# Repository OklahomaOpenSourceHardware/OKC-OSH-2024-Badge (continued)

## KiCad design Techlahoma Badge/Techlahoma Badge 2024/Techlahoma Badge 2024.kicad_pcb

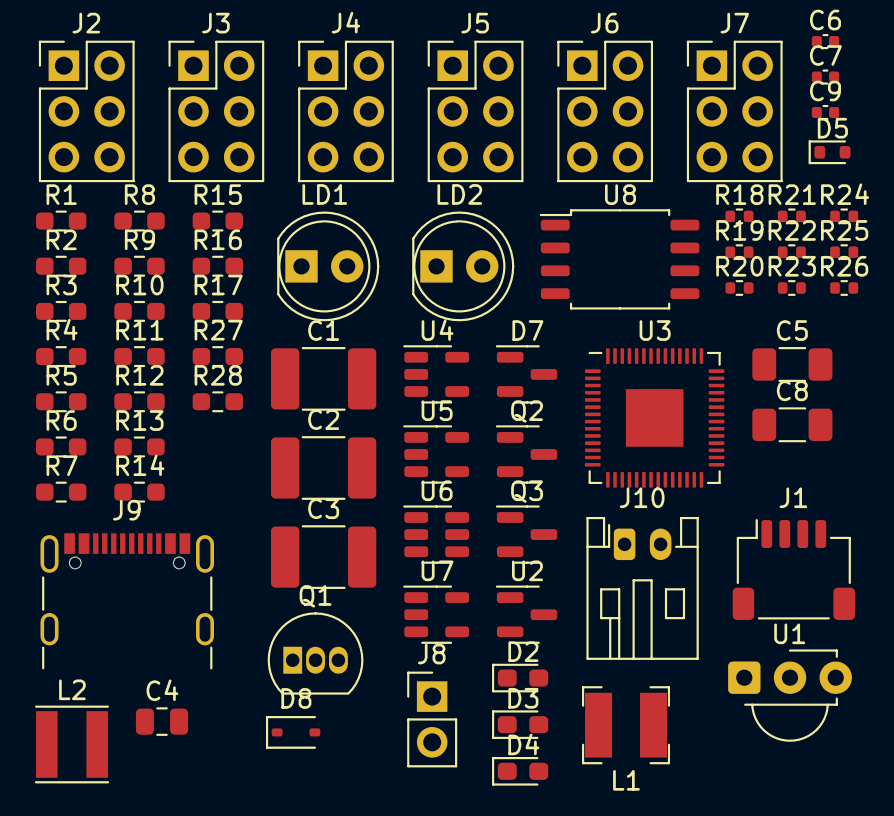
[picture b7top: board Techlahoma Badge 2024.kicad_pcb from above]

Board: 2 copper layers, 68 parts (0 on the bottom side), 43 nets, no tracks yet.

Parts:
C1, C2: 4.7u; C_1812_4532Metric_Pad1.57x3.40mm_HandSolder
C3: C; C_1812_4532Metric_Pad1.57x3.40mm_HandSolder
C4: 4.7u; C_0805_2012Metric
C5, C8: 10u; C_1206_3216Metric_Pad1.33x1.80mm_HandSolder
C6: 6.8p; C_0402_1005Metric
C7: 0.01u; C_0402_1005Metric
C9: 0.1u; C_0402_1005Metric
D2, D3, D4: LED; LED_0603_1608Metric_Pad1.05x0.95mm_HandSolder
D5: ESD5Zxx; D_SOD-523
D7: D_Schottky_Small; SOT-23
D8: 3.3v_TVS; D_SOD-323
J1: I2C; JST_SH_SM04B-SRSS-TB_1x04-1MP_P1.00mm_Horizontal
J2, J3, J4, J5, J6, J7: Conn_02x03_Counter_Clockwise; PinHeader_2x03_P2.54mm_Vertical
J8: Conn_01x02_Male; PinHeader_1x02_P2.54mm_Vertical
J9: USB_C_Receptacle_USB2.0; USB_C_Receptacle_GCT_USB4105-xx-A_16P_TopMnt_Horizontal
J10: Conn_01x02_Male; JST_PH_S2B-PH-K_1x02_P2.00mm_Horizontal
L1: 2.2u; L_Bourns-SRN4018
L2: 2.2uH; L_Taiyo-Yuden_MD-4040
LD1, LD2: SPL_PL90; LED_D5.0mm
Q1: 2N3904; TO-92_Inline
Q2: PMOS; SOT-23
Q3: MMBT3906; SOT-23
R1, R2, R3, R4, R5, R9, R13, R14, R15, R16, R17: 220; R_0603_1608Metric_Pad0.98x0.95mm_HandSolder
R6: 100; R_0603_1608Metric_Pad0.98x0.95mm_HandSolder
R7, R8, R27, R28: 1.8k; R_0603_1608Metric_Pad0.98x0.95mm_HandSolder
R10, R11, R12: 3.3; R_0603_1608Metric_Pad0.98x0.95mm_HandSolder
R18, R19, R26: 5.1k; R_0402_1005Metric
R20: 680k; R_0402_1005Metric
R21: 150K; R_0402_1005Metric
R22, R23: 15K; R_0402_1005Metric
R24, R25: 27; R_0402_1005Metric
U1: TSOP382xx; Vishay_MINICAST-3Pin
U2: LM4040DBZ-5; SOT-23
U3: RP2040; QFN-56-1EP_7x7mm_P0.4mm_EP3.2x3.2mm
U4: TPS613221ADBV; SOT-23-5
U5: TLV62569DBV; SOT-23-5
U6: SN65220; SOT-23-6
U7: MCP73811T-420I-OT; SOT-23-5
U8: W25Q128JVS; SOIC-8_5.23x5.23mm_P1.27mm

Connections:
+3V3: C3.1, C5.1, C6.1, C7.1, C8.1, C9.1, D8.1 (A1), J1.2, L2.2, R6.2, R8.1, R10.1, R20.2, R27.1, U2.1 (K), U3.1 (IOVDD), U3.10 (IOVDD), U3.22 (IOVDD), U3.33 (IOVDD), U3.42 (IOVDD), U3.43 (ADC_AVDD), U3.44 (VREG_IN), U3.48 (USB_VDD), U3.49 (IOVDD), U4.4 (VOUT), U8.8 (VCC)
/Battery_VIN: C2.1, J2.1, J3.1, J4.1, J5.1, J6.1, J7.1, J8.1, L1.1
/CS/MISO: J2.5, J3.5, J4.5, J5.5, J6.5, J7.5, R1.2, R13.2, R14.2, R15.2, R16.2, R17.2
/D+: J9.A6 (D+), J9.B6 (D+), R22.1, R24.1, U6.1, U6.6 (A)
/D-: J9.A7 (D-), J9.B7 (D-), R23.2, R25.1, U6.3, U6.4 (B)
/SCL/SCK: J2.4, J3.4, J4.4, J5.4, J6.4, J7.4
/SD0: U3.53 (QSPI_SD0), U8.5 (DI(IO0))
/SD1: U3.55 (QSPI_SD1), U8.2 (DO(IO1))
/SD2: U3.54 (QSPI_SD2), U8.3 (IO2)
/SD3: U3.51 (QSPI_SD3), U8.7 (IO3)
/SDA/MOSI/DATA: J2.3, J3.3, J4.3, J5.3, J6.3, J7.3
/Switched_Power: C4.1, U5.1 (EN), U5.4 (VIN)
/UPDI: J2.6, J3.6, J4.6, J5.6, J6.6, J7.6, R1.1, R5.2, R13.1, R14.1, R15.1, R16.1, R17.1
/UPDI_protected: D5.1 (K), D7.2 (A), Q1.2 (B), R5.1, R7.1
/USB_D+: R24.2, U3.47 (USB_DP)
/USB_D-: R25.2, U3.46 (USB_DM)
/USB_pwr: J9.A4 (VBUS), J9.A9 (VBUS), J9.B4 (VBUS), J9.B9 (VBUS)
/VBAT: J10.1, U7.3 (VBAT)
/V_USB: U7.1 (CEN), U7.4 (VDD)
/spi_clk: U3.52 (QSPI_SCLK), U8.6 (CLK)
GND: C2.2, C3.2, C4.2, C5.2, C7.2, C8.2, C9.2, D5.2 (A), D8.2 (A2), J1.1, J1.MP (Pin_5), J2.2, J3.2, J4.2, J5.2, J6.2, J7.2, J8.2, J9.A1 (GND), J9.A12 (GND), J9.B1 (GND), J9.B12 (GND), J9.S1 (SHIELD), J10.2, R2.2, R3.2, R4.2, R18.2, R19.2, R21.1, R22.2, R23.1, R26.1, U3.19 (TESTEN), U3.57 (GND), U4.2 (GND), U5.2 (GND), U6.2 (GND), U6.5 (GND), U7.2 (VSS), U8.4 (GND)
unnamed: D2.1 (K), R2.1
unnamed: D3.1 (K), R3.1
unnamed: D4.1 (K), R4.1
unnamed: J9.A5 (CC1), R19.1
unnamed: J9.B5 (CC2), R18.1
unnamed: LD1.2 (A), R11.2
unnamed: LD1.1 (C), LD2.1 (C), Q2.3 (S)
unnamed: LD2.2 (A), R12.2
unnamed: Q1.3 (C), R8.2, R9.1
unnamed: Q1.1 (E), Q2.1 (D)
unnamed: Q3.1 (B), R9.2, U2.2 (A)
unnamed: Q3.3 (C), R11.1, R12.1
unnamed: Q3.2 (E), R10.2
unnamed: C1.2, U1.2 (GND)
unnamed: C1.1, R6.1, U1.3 (Vs)
unnamed: U3.23 (DVDD), U3.50 (DVDD)
unnamed: R27.2, U3.26 (RUN)
unnamed: L1.2, U4.1 (SW)
unnamed: C6.2, R20.1, R21.2, U5.5 (FB)
unnamed: L2.1, U5.3 (SW)
unnamed: R26.2, U7.5 (PROG)
unnamed: R28.2, U8.1 (~CS)

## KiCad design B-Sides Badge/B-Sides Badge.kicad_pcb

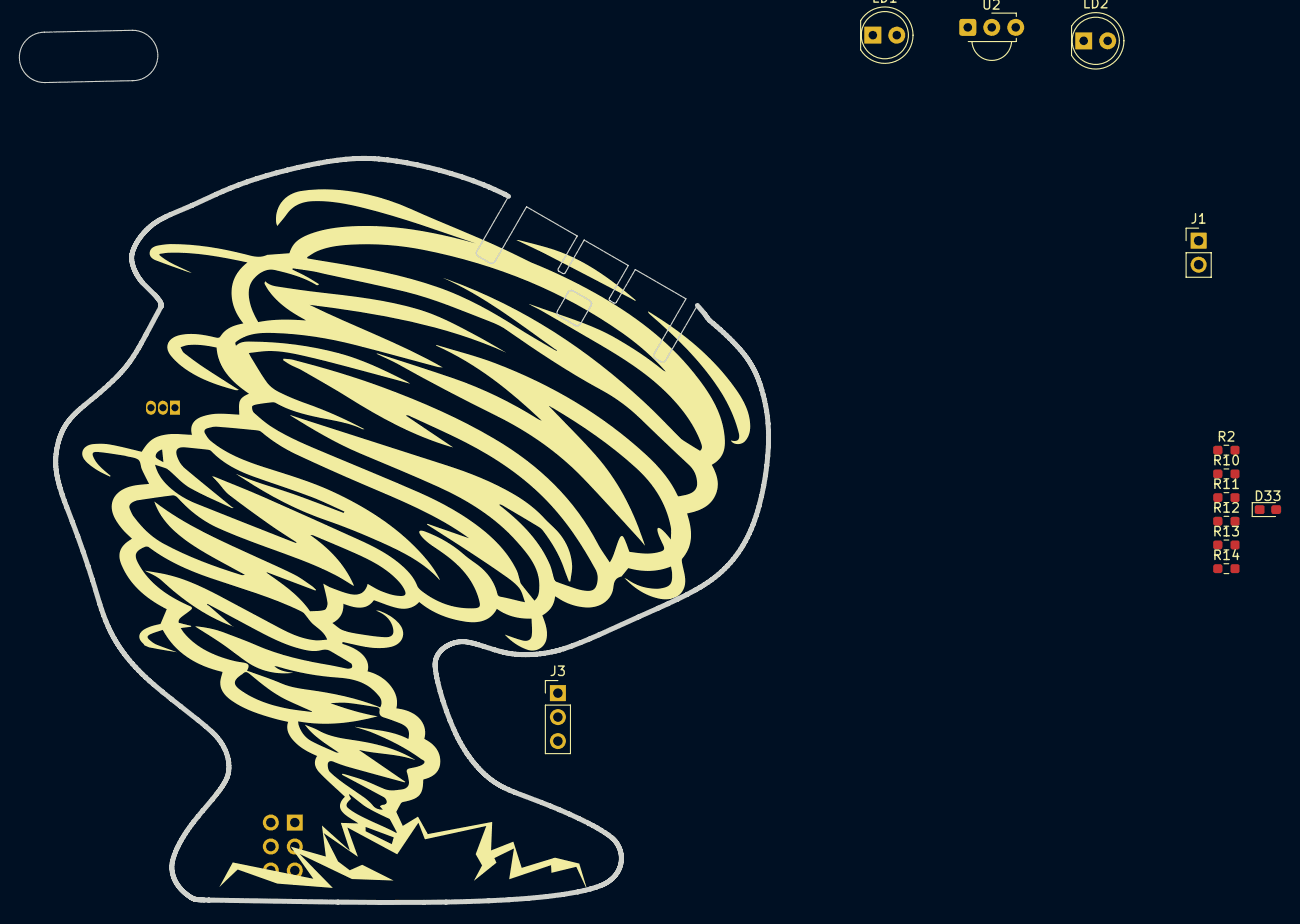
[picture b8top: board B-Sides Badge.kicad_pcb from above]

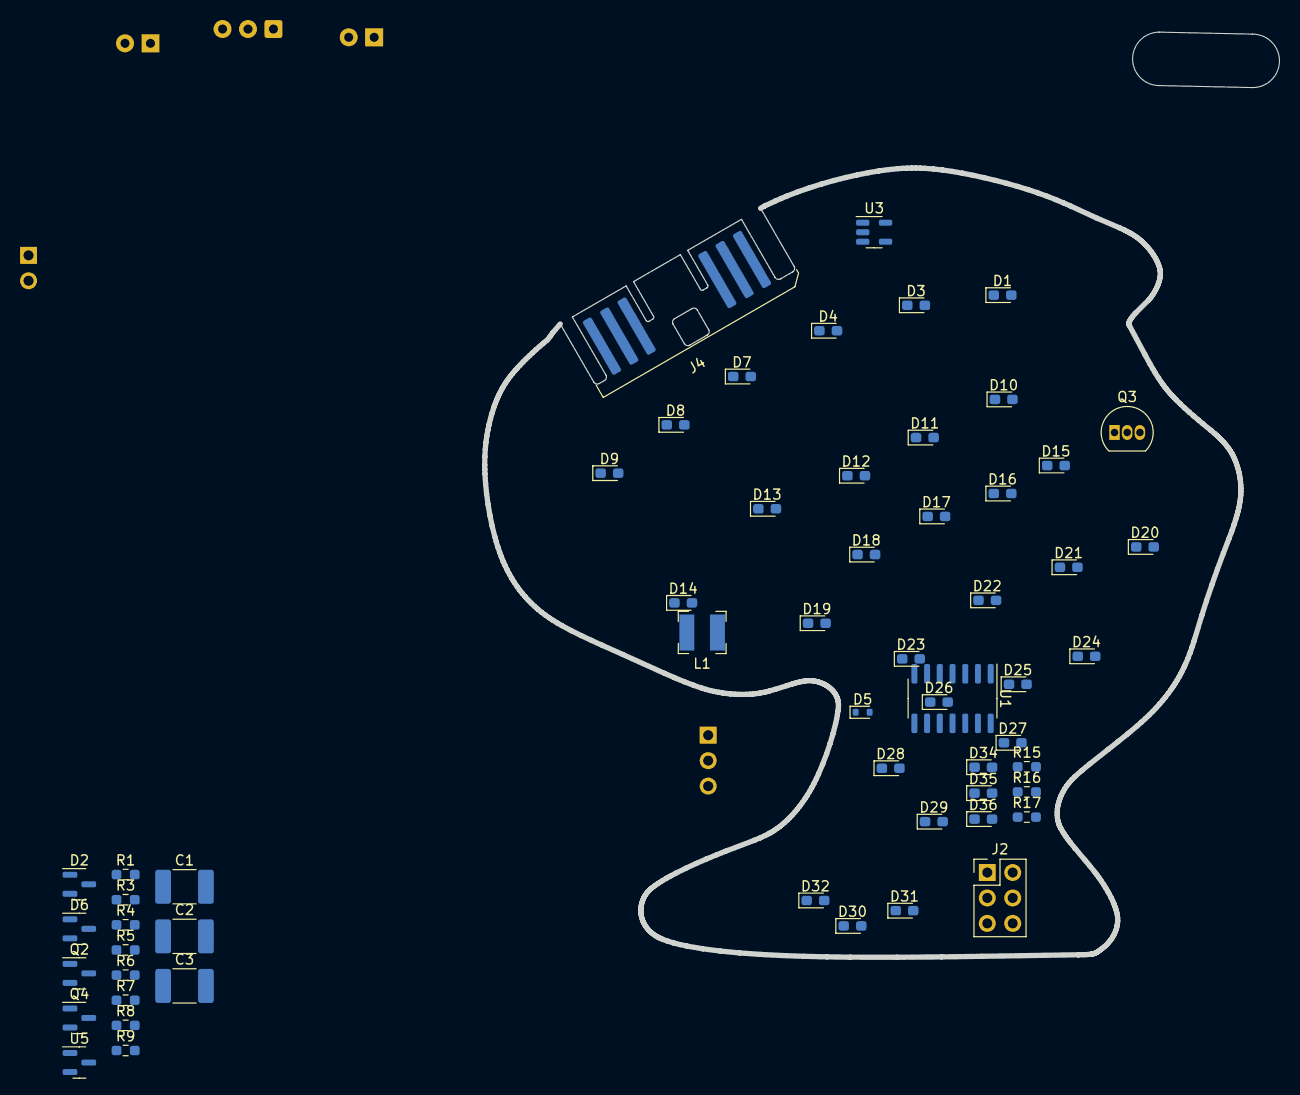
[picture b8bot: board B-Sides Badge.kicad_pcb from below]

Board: 2 copper layers, 79.4 x 92.4 mm, 70 parts (58 on the bottom side), 36 nets, no tracks yet.

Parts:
C1: C; C_1812_4532Metric_Pad1.57x3.40mm_HandSolder
C2, C3: 4.7u; C_1812_4532Metric_Pad1.57x3.40mm_HandSolder
D1, D3, D4, D7, D8, D9, D10, D11, D12, D13, D14, D15, D16, D17, D18, D19, D20, D21, D22, D23, D24, D25, D26, D27, D28, D29, D30, D31, D32, D33, D34, D35, D36: LED; LED_0603_1608Metric_Pad1.05x0.95mm_HandSolder
D2: BAT54C; SOT-23
D5: ESD5Zxx; D_SOD-523
D6: D_Schottky_Small; SOT-23
J1: Conn_01x02_Male; PinHeader_1x02_P2.54mm_Vertical
J2: Conn_02x03_Counter_Clockwise; PinHeader_2x03_P2.54mm_Vertical
J3: Conn_01x02; PinHeader_1x03_P2.54mm_Vertical
J4: Conn_01x06; molex_EDGELOCK_6-CKT
L1: 2.2u; L_Bourns-SRN4018
LD1, LD2: SPL_PL90; LED_D5.0mm
Q2: PMOS; SOT-23
Q3: 2N3904; TO-92_Inline
Q4: MMBT3906; SOT-23
R1, R6: 1.8k; R_0603_1608Metric_Pad0.98x0.95mm_HandSolder
R2, R4, R5, R10, R11, R12, R13, R14, R15, R16, R17: 220; R_0603_1608Metric_Pad0.98x0.95mm_HandSolder
R3: 100; R_0603_1608Metric_Pad0.98x0.95mm_HandSolder
R7, R8, R9: 3.3; R_0603_1608Metric_Pad0.98x0.95mm_HandSolder
U1: ATtiny814-SS; SOIC-14_3.9x8.7mm_P1.27mm
U2: TSOP382xx; Vishay_MINICAST-3Pin
U3: TPS613221ADBV; SOT-23-5
U5: LM4040DBZ-5; SOT-23

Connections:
+3V3: J3.1, J4.1, R3.2, R6.1, R7.1, U1.1 (VCC), U5.1 (K)
/Battery_VIN: C3.1, J1.1, J2.1, J4.2, L1.1
/Charlie_Plex_1: R2.2, U1.11 (PA1)
/Charlie_Plex_2: R10.2, U1.12 (PA2)
/Charlie_Plex_3: R11.2, U1.13 (PA3)
/Charlie_Plex_4: R12.2, U1.2 (PA4)
/Charlie_Plex_5: R13.2, U1.3 (PA5)
/Charlie_Plex_6: R14.2, U1.4 (PA6)
/LED_RED: J2.3, J4.3
/UPDI: J3.2, R4.2, U1.10 (~RESET/PA0)
/UPDI_protected: D5.1 (K), D6.2 (A), Q3.2 (B), R1.1, R1.2, R4.1, U1.5 (PA7)
/led_blue: D36.2 (A), U1.7 (PB2)
/led_green: D35.2 (A), U1.8 (PB1)
/led_red: D34.2 (A), U1.9 (PB0)
GND: C1.2, C2.2, C3.2, D5.2 (A), J1.2, J2.2, J3.3, J4.6, R15.2, R16.2, R17.2, U1.14 (GND), U2.2 (GND), U3.2 (GND)
unnamed: D1.2 (A), D3.1 (K), D4.2 (A), D7.1 (K), D8.2 (A), D10.1 (K), D27.2 (A), D29.2 (A), D30.1 (K), D31.1 (K), R12.1
unnamed: D1.1 (K), D3.2 (A), D9.2 (A), D21.2 (A), D23.2 (A), D24.1 (K), D25.2 (A), D26.1 (K), D28.1 (K), D33.1 (K), R10.1
unnamed: D6.1 (K), U2.1 (OUT)
unnamed: D10.2 (A), D13.2 (A), D14.1 (K), D17.2 (A), D18.1 (K), D19.1 (K), D20.2 (A), D23.1 (K), D24.2 (A), D27.1 (K), R11.1
unnamed: D7.2 (A), D8.1 (K), D11.2 (A), D12.1 (K), D15.2 (A), D19.2 (A), D20.1 (K), D21.1 (K), D22.1 (K), D33.2 (A), R2.1
unnamed: D4.1 (K), D9.1 (K), D11.1 (K), D12.2 (A), D13.1 (K), D14.2 (A), D16.1 (K), D28.2 (A), D31.2 (A), D32.2 (A), R14.1
unnamed: D15.1 (K), D16.2 (A), D17.1 (K), D18.2 (A), D22.2 (A), D25.1 (K), D26.2 (A), D29.1 (K), D30.2 (A), D32.1 (K), R13.1
unnamed: D34.1 (K), R15.1
unnamed: D35.1 (K), R16.1
unnamed: D36.1 (K), R17.1
unnamed: LD1.2 (A), R9.2
unnamed: LD1.1 (C), LD2.1 (C), Q2.3 (S)
unnamed: LD2.2 (A), R8.2
unnamed: Q2.1 (D), Q3.1 (E)
unnamed: Q3.3 (C), R5.1, R6.2
unnamed: Q4.1 (B), R5.2, U5.2 (A)
unnamed: Q4.3 (C), R8.1, R9.1
unnamed: Q4.2 (E), R7.2
unnamed: C2.1, R3.1, U2.3 (Vs)
unnamed: L1.2, U3.1 (SW)
unnamed: C1.1, U3.4 (VOUT)

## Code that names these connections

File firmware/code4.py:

#latest firmware
#https://github.com/OklahomaOpenSourceHardware/OKC-OSH-2024-Badge/tree/main-2/firmware

#Board files
#https://github.com/OklahomaOpenSourceHardware/OKC-OSH-2024-Badge/tree/main-2/B-Sides%202024
import time
import board
import random
from rainbowio import colorwheel
import neopixel
import digitalio
import pulseio
import adafruit_irremote

# packet format [wait_time_mS,inverse (wait_time_mS), colorwheel(0:255), inverse colorwheel(0:255)]
#each badge has a timeslot 0-255 with a time window of 108mS, and a full cycle of 27.54 seconds
#every approximately 0.5 minutes, the badge will self segrigate into an empty timeslot, and attempt to phase match the incoming pulses

#once locked, the badge will transmit it's chosen color
#the color is selectable by pressing buttons (BTN_0,BTN_1)

#as your badge recieves messages, the color will shift based on the colors of people around you
trigger_microseconds = 108


tornado_pixels = 40
SAO_2024_pixels = 4






#GPIO0 button 0


#GPIO1 button 1


#GPIO2 SDA_QUICC
#GPIO3 SCL_QUICC

#GPIO4 USBBOOT

#GPIO5 SAO_EN(False), pull down to disable SAO power

#GPIO6 SAO_TX_45
pixels_SAO_45 = neopixel.NeoPixel(board.GP6, SAO_2024_pixels, brightness=0.05, auto_write=False)
#GPIO7 SAO_RX_45
#GPIO8 SAO_SCL
#GPIO9 SAO_SDA
#GPIO10 DIO_LV
pixels_DIO_Tornado = neopixel.NeoPixel(board.GP10, tornado_pixels, brightness=0.05, auto_write=False)

#GPIO13 LED_RED, simple led, set pin value high/True to light the led
pin_led = digitalio.DigitalInOut(board.GP13)
pin_led.direction = digitalio.Direction.OUTPUT

#GPIO19 SAO_TX_H
pixels_SAO_H = neopixel.NeoPixel(board.GP19, SAO_2024_pixels, brightness=0.05, auto_write=False)
#GPIO18 SAO_RX_H

#GPIO23 (False), negative logic, has external pull up resistor
pulsein = pulseio.PulseIn(board.GP23, maxlen=200, idle_state=True)

#GPIO24 IR_led_driver(True) positive logic, drive high to turn on IR LEDs
pulseout = pulseio.PulseOut(board.GP24, frequency=38000, duty_cycle=2 ** 15)

#GPIO25 LED_EN(True), this pin enabled the fuse/switch  for the SAO and neopixel leds
pin = digitalio.DigitalInOut(board.GP25)
pin.direction = digitalio.Direction.OUTPUT

#GPIO28 PWR_FLT, pulled low when fault is present on the LED lines
pin_pwr = digitalio.DigitalInOut(board.GP28)
pin_pwr.switch_to_input()
pin_pwr.direction = digitalio.Direction.INPUT


encoder = adafruit_irremote.GenericTransmit(header=[9582, 4529], one=[559, 559], zero=[559, 1699], trail=105)
decoder = adafruit_irremote.GenericDecode()
pulsein.clear()
pulsein.resume() #trigger_microseconds
nonblocking_decoder = adafruit_irremote.NonblockingGenericDecode(pulsein)

t0 = next_heartbeat = time.monotonic()


def color_chase(pixels, color, wait):
    for i in range(num_pixels):
        pixels[i] = color
        time.sleep(wait)
        pixels.show()
    time.sleep(0.1)


def rainbow_cycle(wait):
    for j in range(255):
        for i in range(num_pixels):
            rc_index = (i * 256 // num_pixels) + j
            pixels[i] = colorwheel(rc_index & 255)
        pixels.show()
        time.sleep(wait)

def fuzzy_pulse_compare(pulse1, pulse2, fuzzyness=0.2):
    if len(pulse1) != len(pulse2):
        return False
    for i in range(len(pulse1)):
        threshold = int(pulse1[i] * fuzzyness)
        if abs(pulse1[i] - pulse2[i]) > threshold:
            return False
    return True

def bit_invert(n: int) -> int:
    return n ^ ((1 << n.bit_length()) - 1)
#system variables and constants


RED = (255, 0, 0)
YELLOW = (255, 150, 0)
GREEN = (0, 255, 0)
CYAN = (0, 255, 255)
BLUE = (0, 0, 255)
PURPLE = (180, 0, 255)
pin.value = True

color_choice = random.randint(0, 255)
time_slot = random.randint(0, 255)
received_code = [time_slot, bit_invert(time_slot), color_choice, bit_invert(color_choice)] #[random.randint(0, 255),random.randint(0, 255),random.randint(0, 255),random.randint(0, 255)] #[255, 5, 255, 5]
print(received_code)
transmitted_code = received_code
while True:
    
    
    t = time.monotonic()
    if t > next_heartbeat + (time_slot * trigger_microseconds):
        encoder.transmit(pulseout, transmitted_code)    
    for message in nonblocking_decoder.read():

        print(f"t={time.monotonic() - t0:.3} New Message")
        print("Heard", len(message.pulses), "Pulses:", message.pulses)
        print("statistics", (adafruit_irremote.bin_data(message.pulses)))
        if isinstance(message, adafruit_irremote.IRMessage):
            print("Decoded:", message.code)
            try:
                received_code = decoder.decode_bits(message.code)
                print("Decoded:", received_code)
                if(recieved_code[0] == bit_invert(recieved_code[1]) && recieved_code[2] == bit_invert(recieved_code[3])):
                    color_choice = (color_choice+recieved_code[2])/2
                    pin_led.value = True
                    print("success")
                else:
                    pin_led.value = False
                    print("failed")
                for x , y in zip(received_code , transmitted_code ):
                    y = (x+y)/2
        
                print(received_code[1:4])
                print(transmitted_code)
    
            except adafruit_irremote.FailedToDecode:
                print("Failed to decode")
                trigger_microseconds += 1
            except adafruit_irremote.IRNECRepeatException:  # unusual short code!
                print("NEC repeat!")
            except adafruit_irremote.IRDecodeException as e:     # failed to decode
                print("Failed to decode: ", e.args)
        
        elif isinstance(message, adafruit_irremote.NECRepeatIRMessage):
            print("NEC repeat!")
        elif isinstance(message, adafruit_irremote.UnparseableIRMessage):
            print("Failed to decode", message.reason)
        print("----------------------------")
   
    # This heartbeat confirms that we are not blocked somewhere above.
    t = time.monotonic()
    if t > next_heartbeat:
        print(f"t={time.monotonic() - t0:.3} Heartbeat")
        next_heartbeat = t + 0.1

  
 
        
    
    
  
    color_chase(pixels_DIO_Tornado,color_choice-1, 0.1)
    color_chase(pixels_DIO_Tornado,color_choice, 0.1)
    color_chase(pixels_DIO_Tornado,color_choice+1, 0.1)
    # Clear the rest
    #pulsein.clear()
    # Resume with an 80 microsecond active pulse
    #pulsein.resume() #trigger_microseconds
  #  time.sleep(1)  
#    if pin_pwr.value == True :
#        pin_led.value = False
#    if pin_pwr.value == False :
#        pin_led.value = True
    
   # pixels.fill(RED)
   # pixels.show()
    # Increase or decrease to change the speed of the solid color change.
   # time.sleep(1)
   # pixels.fill(GREEN)
   # pixels.show()
   # time.sleep(1)
   # pixels.fill(BLUE)
   # pixels.show()
   # time.sleep(1)

   # color_chase(RED, 0.1)  # Increase the number to slow down the color chase
   # color_chase(YELLOW, 0.1)
   # color_chase(GREEN, 0.1)
   # color_chase(CYAN, 0.1)
   # color_chase(BLUE, 0.1)
   # color_chase(PURPLE, 0.1)

    #rainbow_cycle(0)  # Increase the number to slow down the rainbow

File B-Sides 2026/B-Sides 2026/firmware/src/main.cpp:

#include <Arduino.h>
#include <Adafruit_NeoPixel.h>
#include <avr/sleep.h>
#include <avr/io.h>
#include <ptc.h>

// ---------------------------------------------------------
// DEBUG TOGGLE: Comment out this line to DISABLE deep sleep
// and timers to verify core functionality.
// ---------------------------------------------------------
//#define ENABLE_LOW_POWER

#define PIEZO_PIN   PIN_PA1
#define TOUCH_PIN   PIN_PA4
#define LED_DATA    PIN_PB4
#define LED_PWR_EN  PIN_PB5
#define SDA_SAO     PIN_PB2
#define SCL_SAO     PIN_PB3
#define PC3_SAO     PIN_PC3
#define NUM_LEDS    4

Adafruit_NeoPixel strip(NUM_LEDS, LED_DATA, NEO_GRB + NEO_KHZ800);
uint32_t nextSleep = 10000;
cap_sensor_t touch_node;

long readVcc() {
  analogReference(INTERNAL1V1);
  
  ADC0.MUXPOS = ADC_MUXPOS_AIN10_gc;
  ADC0.CTRLA = ADC_ENABLE_bm;
  ADC0.COMMAND = ADC_STCONV_bm;
  
  while(!(ADC0.INTFLAGS & ADC_RESRDY_bm));
  uint16_t reading = ADC0.RES;

  ADC0.CTRLA &= ~ADC_ENABLE_bm; 

  if (reading == 0) return 0;
  return (11264000L / reading);
}

void setLedPower(bool on) {
  if (on) {
    pinMode(LED_PWR_EN, OUTPUT);
    digitalWrite(LED_PWR_EN, LOW); 
    delay(10); 
    strip.begin();
    strip.show();
  } else {
    digitalWrite(LED_PWR_EN, HIGH);
    pinMode(LED_DATA, OUTPUT); 
    digitalWrite(LED_DATA, LOW);
  }
}

void playStarTrekChirp() {
  setLedPower(true);
  for (int j = 0; j < 2; j++) {
    int startFreq = (j == 0) ? 800 : 1000;
    for (int i = 0; i < 20; i++) {
      int freq = startFreq + (i * 20);
      tone(PIEZO_PIN, freq);
      for(int l=0; l<NUM_LEDS; l++) strip.setPixelColor(l, 0, 0, i * 12);
      strip.show();
      delay(5);
    }
    noTone(PIEZO_PIN);
    digitalWrite(PIEZO_PIN, LOW); 
    if (j == 0) delay(40);
  }
  setLedPower(false);
}

void ptc_event_cb_touch(const ptc_cb_event_t eventType, cap_sensor_t *node) {
  if (PTC_CB_EVENT_TOUCH_DETECT == eventType) {
    playStarTrekChirp();
  } 
}

void ptc_event_cb_calibration(const ptc_cb_event_t eventType, cap_sensor_t* node)  {
  if (PTC_CB_EVENT_ERR_CALIB_LOW == eventType || PTC_CB_EVENT_ERR_CALIB_HIGH == eventType) {
    playStarTrekChirp(); 
  }
}

void setup() {
  ptc_add_selfcap_node(&touch_node, 0, PIN_TO_PTC(TOUCH_PIN));

  uint32_t start_time = millis();
  while (millis() - start_time < 1000) {
      ptc_process(millis());
  }

#ifdef ENABLE_LOW_POWER
  // --- LOW POWER CONFIGURATION ---
  _PROTECTED_WRITE(BOD.CTRLA, BOD_SLEEP_DIS_gc);

  RTC.CLKSEL = RTC_CLKSEL_INT32K_gc;
  while (RTC.STATUS > 0); 
  
  RTC.PITCTRLA = RTC_PERIOD_CYC4096_gc | RTC_PITEN_bm;
  
  EVSYS.ASYNCCH3 = EVSYS_ASYNCCH3_PIT_DIV4096_gc;
  EVSYS.ASYNCUSER1 = EVSYS_ASYNCUSER1_ASYNCCH3_gc;
  
  SLPCTRL.CTRLA = SLEEP_MODE_STANDBY | SLPCTRL_SEN_bm;
#endif

  pinMode(LED_PWR_EN, OUTPUT);
  setLedPower(false);
  pinMode(PIEZO_PIN, OUTPUT);
  digitalWrite(PIEZO_PIN, LOW);
}

void loop() {
  ptc_process(millis());    

#ifdef ENABLE_LOW_POWER
  // Low power sleep
  set_sleep_mode(SLEEP_MODE_STANDBY);
  sleep_enable();
  sleep_cpu();
  sleep_disable();
#else
  // When awake, add a tiny delay to prevent the loop from running 
  // unnecessarily fast and masking timing issues.
  delay(10);
#endif
}

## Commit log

2023-10-16 cleanded up IR transmitter files, still looking to optimize led diver
2023-10-16 updated board layout and first crack at badge slot
2023-12-09 combined everyting into one repo, will rename PCB badges 2024 or something similar
2024-02-08 in progress update
2024-02-09 routing changes and layout
2024-02-09 added battery holder
2024-02-12 layout changes
2024-02-21 updated outline, gerbers and schematic
2024-02-22 got all DRC errors resolved
    candidate for JLCPCB price check
2024-02-25 jlcpcb as ordered
2024-02-25 added as sent gerbers
2024-02-25 project archive
2024-02-26 updated BOM in schematic. added updated logos for 2024 badge
2024-02-26 pushed changes from schematic to pcb
2024-02-27 added SAO corrections, added 2024 badge lots of minor fixes
2024-02-29 fixed ws2812b-2020 such that it has the correct pin out for the schematic part
2024-03-02 commit before migrating to kicad 8
2024-03-05 intermediary push
2024-03-08 produ ction v2
2024-03-25 staging changed files
2024-03-25 adding git ignore
2024-03-25 added v1 schematic
2024-03-29 adding in circuit python firmware
2024-04-02 updated firmware crashes currently
2024-04-02 async code
2024-04-02 firmware load
2025-01-31 updated things, lots of chages
2025-01-31 baby steps
2025-01-31 fixed the keepout hand edited group
2025-02-04 proto rev 0.1
2025-02-17 updated file path and adding initial firmware
2025-02-20 updated firmware to use interrupts
2025-02-23 Add files via upload
    test files adding blink
2025-02-24 seems to be working,
    one odd thing, firmware doesn't stay saved in flash.
2025-02-24 added pdf schematic
2025-02-26 firmware changes and schematic changes
2025-02-27 mostly done, but missing cutouts that were hand applied
2025-02-27 fixed missing zone rules, oof
2025-02-28 prod 1.1
    updated led footprint, changed jlcpcb part numbers for availability, updated silk screen
2025-02-28 lotta minor stuff
2025-03-03 Migrated phototransitor code from attiny
2025-03-03 added v1.1 schematic
2025-03-05 move ADC to A1,A2, add filter
2025-03-05 animate frames; add html
2025-03-07 add button handler
2025-03-08 mpu6050 demo
2025-03-09 add oled code
2025-03-09 move to screen based architecture
2025-03-09 change default screen to 11
2025-03-10 remove pinMode to reduce code size
2025-03-27 staging progress
    updated framerate, probably need to make it variable or pause animations or bypass animations for effects that don't need it
    breathing isnt' correct, but the counting effect is neat, may reuse it for something else
    the game class is non functional, needs to be turned into a simple state machine that looks for different pattern combos
    keeping the current menu state machine since it allows for 11 different mini pattern games
    todo:
    need to make the reset more responsive, I tried to implement a hold function to reset but that didn't work as intended
2025-03-28 remove oled use
2025-03-28 remove unused code
2025-03-28 fix long click
2025-03-28 memoryless BreathingScreen
2025-03-28 add sha256 lib
2025-03-28 add game
2025-03-29 revert max amount of frames and rate; tx
2025-03-29 updated gitignore
2025-03-29 Flash programming
2025-03-30 added hashing function of events, adjusted the LED's so they don't immediately turn on and there's a zeroth position available.
    can't tell if the hash function is working yet.
2025-03-30 different game
2025-03-30 added hashes added progress flags fixed it so success resets the game so the next one can be entered in
2025-03-30 corrected hash 2
2025-03-30 special codes
2025-03-30 added hidden menu in no#2
2025-04-01 added ascii firmware credits
2025-07-10 minor changes,
    "shouldn't affect board, but might revert if an unintended change crept in"
2026-02-16 fixed missing hash
2026-03-02 adding firmware
2026-03-03 release that got sent to manufacturing
2026-03-11 firmware compiles here
2026-03-11 added files for manufacturing that weren't previously added
2026-03-12 addng 2026 manufacturing files
2026-03-12 firmware update, works but drains battery
2026-04-13 debugging code
2026-04-14 final fix, current revision has backwards led mosfet, only gets 6 days of runtime, with fix would get 6 months.
2026-04-21 fixed win deploy
